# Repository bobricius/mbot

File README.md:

# mbot

2D actuator move micro robot in X/Y 2D space
Less than 10$ educational platform with micro magnetic robot (mBot), 
only 6 GPIO to move in unlimited X/Y 2D space

Great for physical education for languages like Karel and make 
SKOBAN game or solve acrylic cutted labyrinth. 

My project not violating SRI international patent 
(maybe, I am not patent expert) 

There is differences: 

- I am using another moving track configutation 
- Control is 3-phase unipolar against 4-phase bipolar 
- My manipulator (mBot) use 4 magnets and not levitating 
- For move in one dimension I need only 3x Mosfets connected to any MCU 
(Arduino Atmega328, Stm32, MSP430, ESP XXXX) 
- 6 GPIO to move in X/Y 2D space 
- Moving board can be produced in any fab, it is just only PCB board 8/8mil 
- IT IS CHEAP

PROJECT PAGE

https://hackaday.io/project/154496-2d-actuator-move-micro-robot-in-xy-2d-space

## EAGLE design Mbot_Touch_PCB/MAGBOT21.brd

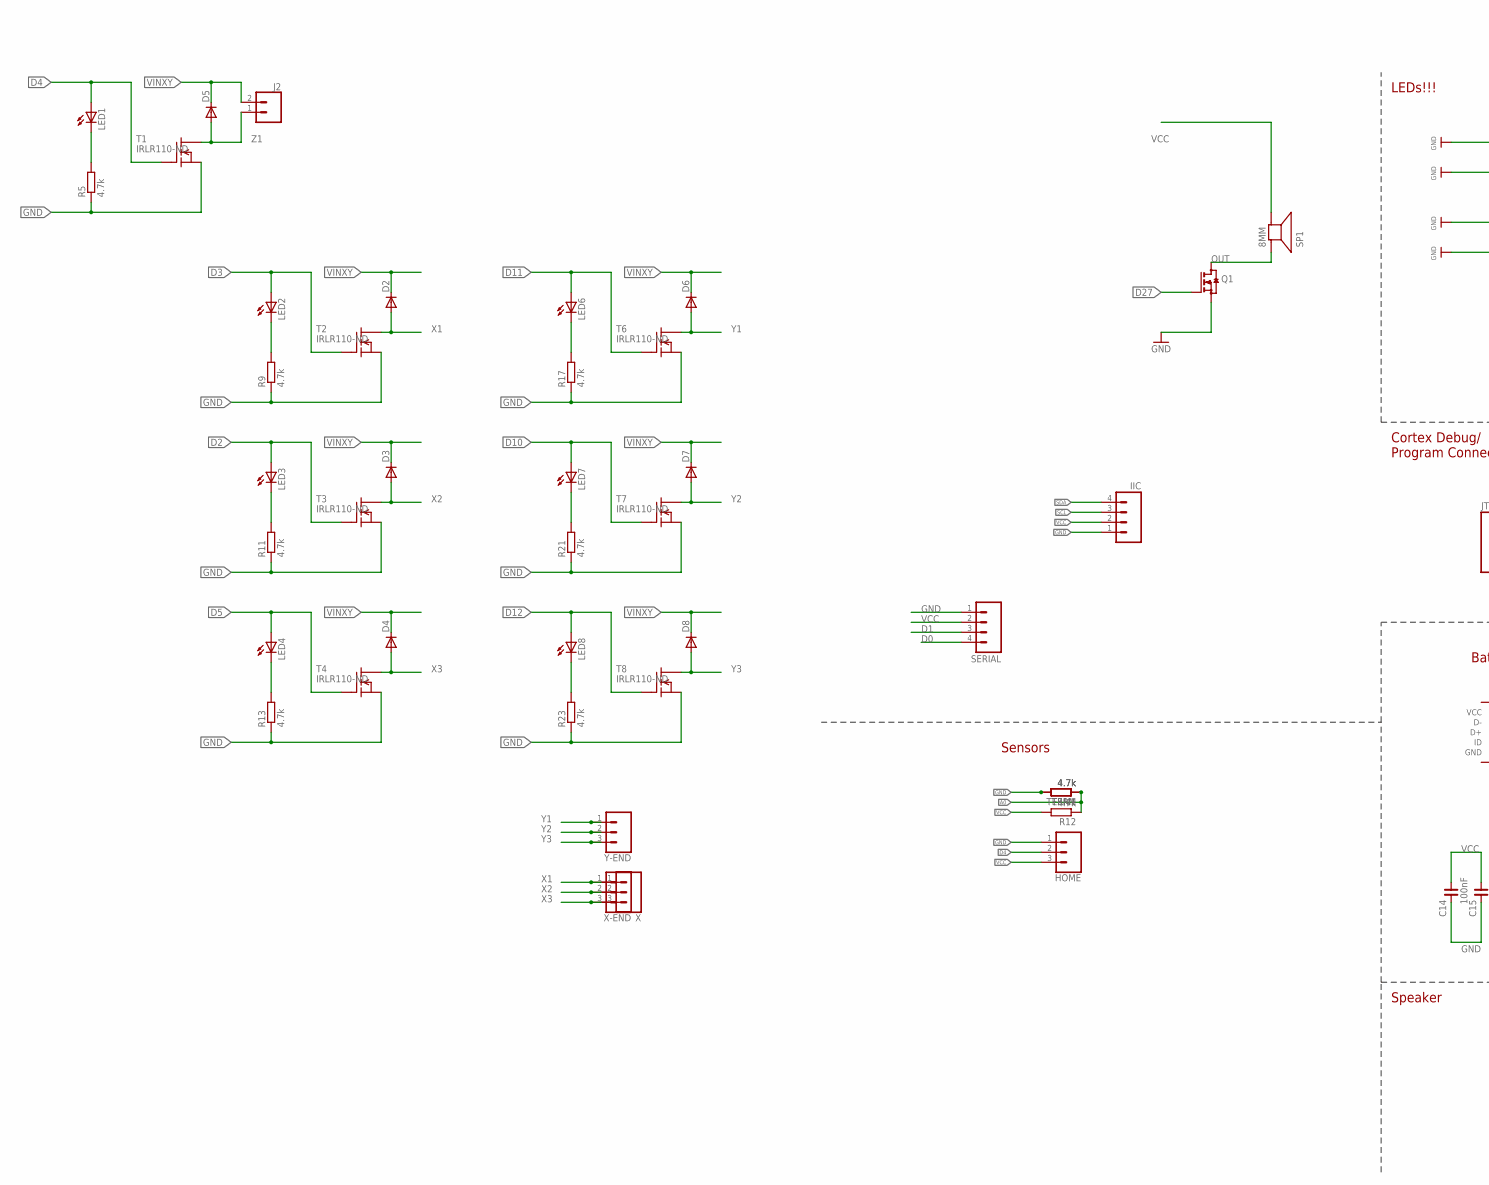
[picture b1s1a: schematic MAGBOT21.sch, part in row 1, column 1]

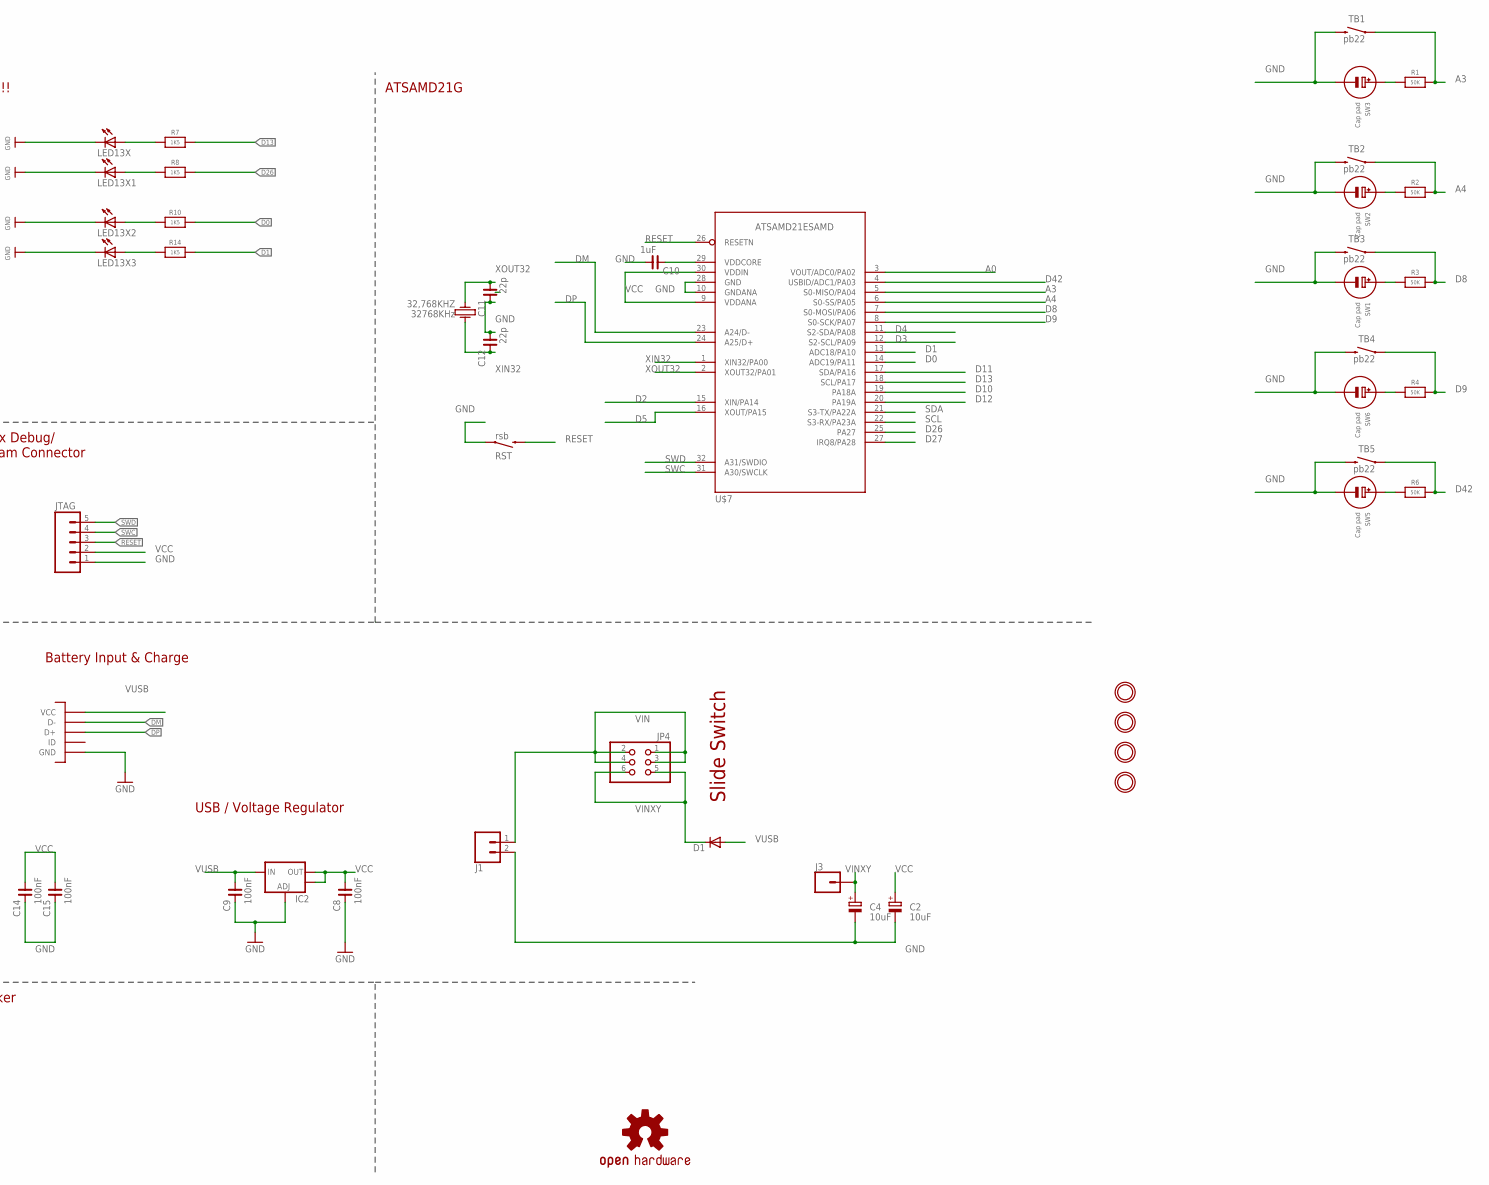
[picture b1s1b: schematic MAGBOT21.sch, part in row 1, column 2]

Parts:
32,768KHZ: 32768KHz; KX-327LT
C2, C4: 10uF; 153CLV-0605
C8, C9: 100nF; C0603
C10: 1uF; C0805
C11, C12: 22p; C0805
C14, C15: 100nF; C0805
D1, D2, D3, D4, D5, D6, D7, D8: DIODE-DO214AC; DO214AC
HOME: CONN_031X03_NO_SILK; 1X03_NO_SILK
IC2: V_REG_LM1117SOT223; SOT223
IIC: M041X04_NO_SILK; 1X04_NO_SILK
J1, J2: CONN_02PTH3; 1X02_LONGPADS
J3: CONN_01PTH_NO_SILK_KIT; 1X01NS_KIT
JP4: PINHD-2X3; 2X03
JTAG: M051.27MM; 1X05-1.27MM
LED1, LED2, LED3, LED4, LED6, LED7, LED8, LED13X, LED13X1: LEDCHIPLED_0805; CHIPLED_0805
LED13X2, LED13X3: LEDCHIPLED_0603; CHIPLED_0603
LOGO3: OSHW-LOGOS; OSHW-LOGO-S
Q1: BSS123; SOT23
R1, R2, R3, R4, R6: 50K; _0805
R5, R9, R11, R12, R13, R17, R21, R23: 4.7k; R0603
R7: 1K5; _0805MP
R8: 1K5; 0603-NO
R10, R14: 1K5; _0603MP
RST: rsb; TACTILE_SWITCH_SMD-3
SERIAL: M041X04_NO_SILK; 1X04_NO_SILK
SP1: 8MM; BUZZER_SMT_5MM
SW1, SW2, SW3, SW5, SW6: Cap pad; CAPTOUCH_SIMPLE_12.5MM
T1, T2, T3, T4, T6, T7, T8: IRLR110-ND; TO252
TB1, TB2, TB3, TB4, TB5: pb22; TACTILE_SWITCH_SMD-3
TERM, TERM1: 4.7k; R0805W
U$3, U$4, U$8, U$10: MOUNTINGHOLE2.0; MOUNTINGHOLE_2.0_PLATED
U$5: MICROUSB; MICRO_B
U$7: ATSAMD21ESAMD; TQFP32-08
X: CONN_031X03_NO_SILK; 1X03_NO_SILK
X-END: CONN_031X03_NO_SILK; 1X03_NO_SILK
Y-END: CONN_031X03_NO_SILK; 1X03_NO_SILK

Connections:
A0: R12.1, TERM.1, TERM1.1, U$7.3 (VOUT/ADC0/PA02)
A3: R1.1, TB1.1, U$7.5 (S0-MISO/PA04)
A4: R2.1, TB2.1, U$7.6 (S0-SS/PA05)
D0: R10.1, SERIAL.4, U$7.14 (ADC19/PA11)
D1: R14.1, SERIAL.3, U$7.13 (ADC18/PA10)
D2: LED3.A, T3.1 (G), U$7.15 (XIN/PA14)
D3: LED2.A, T2.1 (G), U$7.12 (S2-SCL/PA09)
D4: HOME.2, LED1.A, T1.1 (G), U$7.11 (S2-SDA/PA08)
D5: LED4.A, T4.1 (G), U$7.16 (XOUT/PA15)
D8: R3.1, TB3.1, U$7.7 (S0-MOSI/PA06)
D9: R4.1, TB4.1, U$7.8 (S0-SCK/PA07)
D10: LED7.A, T7.1 (G), U$7.19 (PA18A)
D11: LED6.A, T6.1 (G), U$7.17 (SDA/PA16)
D12: LED8.A, T8.1 (G), U$7.20 (PA19A)
D13: R7.1, U$7.18 (SCL/PA17)
D26: R8.1, U$7.25 (PA27)
D27: Q1.1 (G), U$7.27 (IRQ8/PA28)
D42: R6.1, TB5.1, U$7.4 (USBID/ADC1/PA03)
DM: U$5.P2 (D-), U$7.23 (A24/D-)
DP: U$5.P3 (D+), U$7.24 (A25/D+)
GND: C2.-, C4.-, C8.2, C9.2, C10.1, C11.2, C12.1, C14.2, C15.2, HOME.1, IC2.1 (ADJ), IIC.1, J1.2, JTAG.1, LED13X.C, LED13X1.C, LED13X2.C, LED13X3.C, Q1.2 (S), R5.1, R9.1, R11.1, R13.1, R17.1, R21.1, R23.1, RST.1, SERIAL.1, SW1.G (-), SW2.G (-), SW3.G (-), SW5.G (-), SW6.G (-), T1.2 (S), T2.2 (S), T3.2 (S), T4.2 (S), T6.2 (S), T7.2 (S), T8.2 (S), TB1.4 (2), TB2.4 (2), TB3.4 (2), TB4.4 (2), TB5.4 (2), TERM.2, TERM1.2, U$5.GND1 (GND), U$5.GND2 (GND), U$5.GND3 (GND), U$5.GND4 (GND), U$5.GND7 (GND), U$5.GND8 (GND), U$5.P5 (GND), U$7.10 (GNDANA), U$7.28 (GND)
unnamed: R6.2, SW5.E (+)
unnamed: R4.2, SW6.E (+)
unnamed: R3.2, SW1.E (+)
unnamed: R2.2, SW2.E (+)
unnamed: R1.2, SW3.E (+)
unnamed: LED13X1.A, R8.2
unnamed: LED2.C, R9.2
unnamed: LED6.C, R17.2
unnamed: C10.2, U$7.29 (VDDCORE)
unnamed: LED3.C, R11.2
unnamed: LED7.C, R21.2
unnamed: LED4.C, R13.2
unnamed: LED8.C, R23.2
unnamed: LED13X.A, R7.2
unnamed: LED1.C, R5.2
unnamed: LED13X2.A, R10.2
unnamed: LED13X3.A, R14.2
OUT: Q1.3 (D), SP1.+
RESET: JTAG.3, RST.4 (2), U$7.26 (RESETN)
SCL: IIC.3, U$7.22 (S3-RX/PA23A)
SDA: IIC.4, U$7.21 (S3-TX/PA22A)
SWC: JTAG.4, U$7.31 (A30/SWCLK)
SWD: JTAG.5, U$7.32 (A31/SWDIO)
VCC: C2.+, C8.1, C14.1, C15.1, HOME.3, IC2.2 (OUT), IC2.4 (OUT), IIC.2, JTAG.2, R12.2, SERIAL.2, SP1.-, U$7.9 (VDDANA), U$7.30 (VDDIN)
VIN: J1.1, JP4.1, JP4.2, JP4.3, JP4.4
VINXY: C4.+, D1.C, D2.C, D3.C, D4.C, D5.C, D6.C, D7.C, D8.C, J2.2, J3.1, JP4.5, JP4.6
VUSB: C9.1, D1.A, IC2.3 (IN), U$5.P1 (VCC)
X1: D2.A, T2.3 (D), X.1, X-END.1
X2: D3.A, T3.3 (D), X.2, X-END.2
X3: D4.A, T4.3 (D), X.3, X-END.3
XIN32: 32,768KHZ.1, C12.2, U$7.1 (XIN32/PA00)
XOUT32: 32,768KHZ.4, C11.1, U$7.2 (XOUT32/PA01)
Y1: D6.A, T6.3 (D), Y-END.1
Y2: D7.A, T7.3 (D), Y-END.2
Y3: D8.A, T8.3 (D), Y-END.3
Z1: D5.A, J2.1, T1.3 (D)

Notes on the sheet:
USB / Voltage Regulator
LEDs!!!
Cortex Debug/ Program Connector
Sensors
ATSAMD21G
Battery Input & Charge
Speaker
Slide Switch

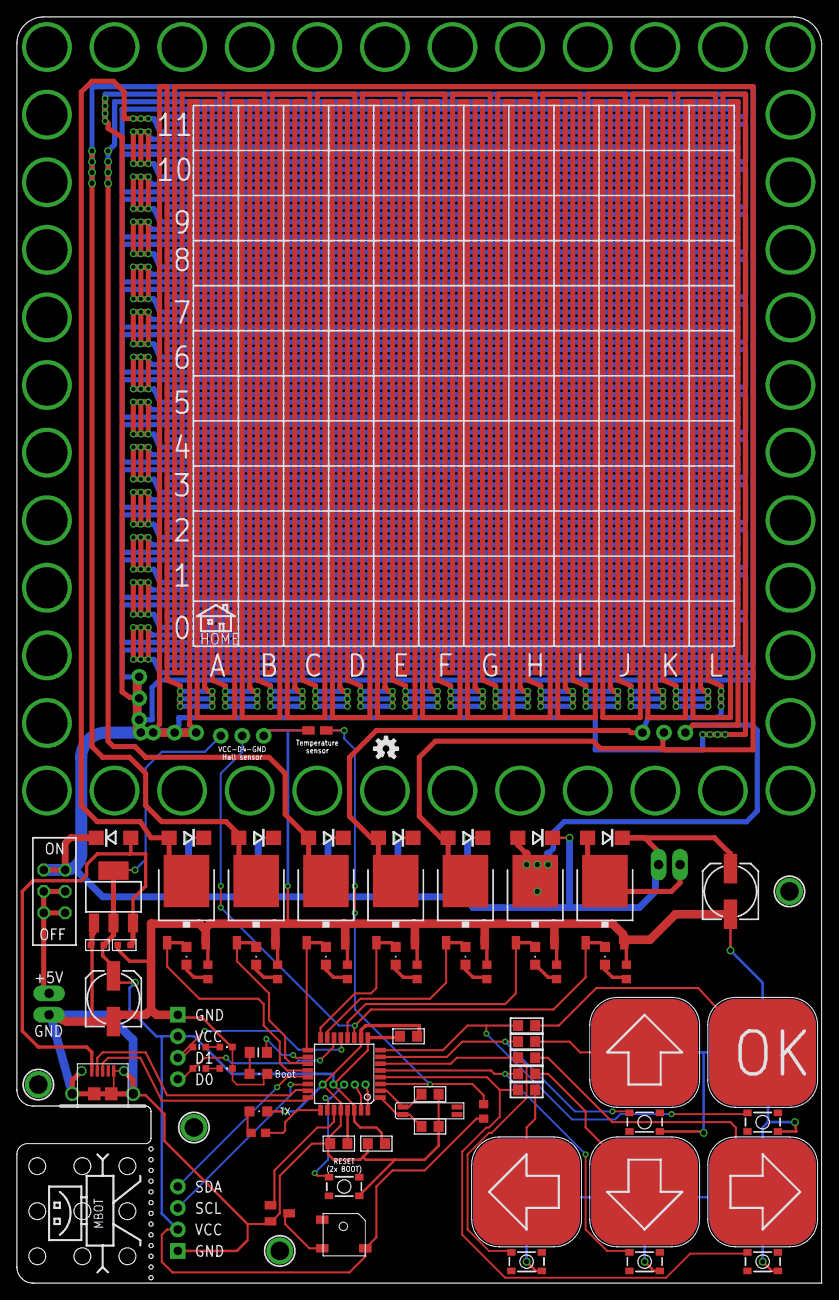
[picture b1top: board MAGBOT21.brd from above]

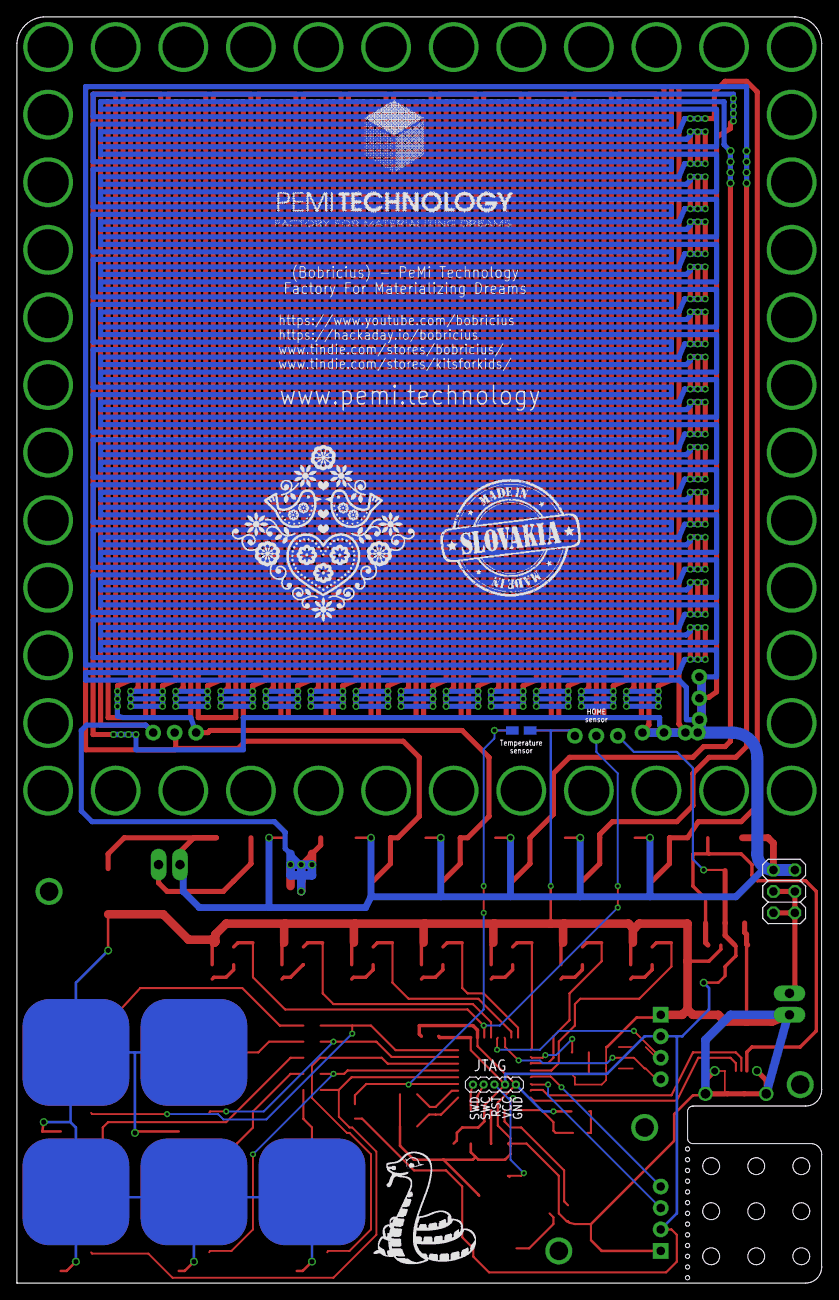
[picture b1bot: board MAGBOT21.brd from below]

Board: 2 copper layers, 95.2 x 149.9 mm, 87 parts (4 on the bottom side), 57 nets.

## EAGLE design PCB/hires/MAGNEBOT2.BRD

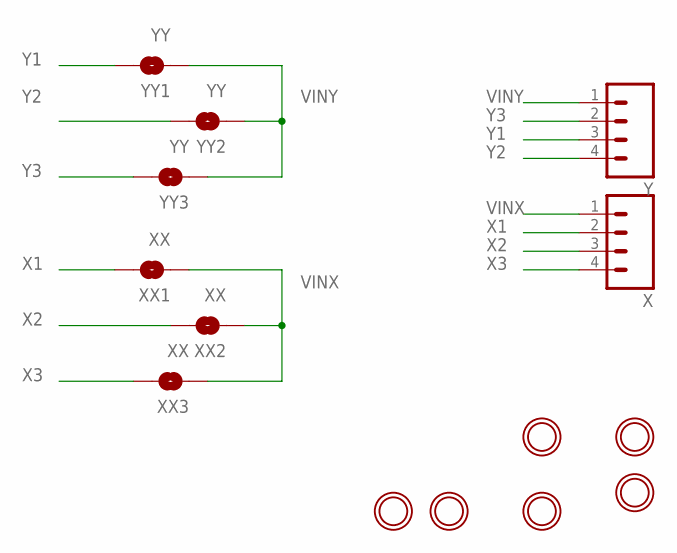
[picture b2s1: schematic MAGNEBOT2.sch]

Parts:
U$1, U$2, U$3, U$4, U$5, U$10: MOUNTINGHOLE2.0; MOUNTINGHOLE_2.0_PLATED
X: M04PTH; 1X04
XX1, XX2, XX3: XX; SJ_2S-TRACE
Y: M04PTH; 1X04
YY1, YY2, YY3: YY; SJ_2S-TRACE

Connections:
VINX: X.1, XX1.1, XX2.1, XX3.1
VINY: Y.1, YY1.1, YY2.1, YY3.1
X1: X.2, XX1.2
X2: X.3, XX2.2
X3: X.4, XX3.2
Y1: Y.3, YY1.2
Y2: Y.4, YY2.2
Y3: Y.2, YY3.2

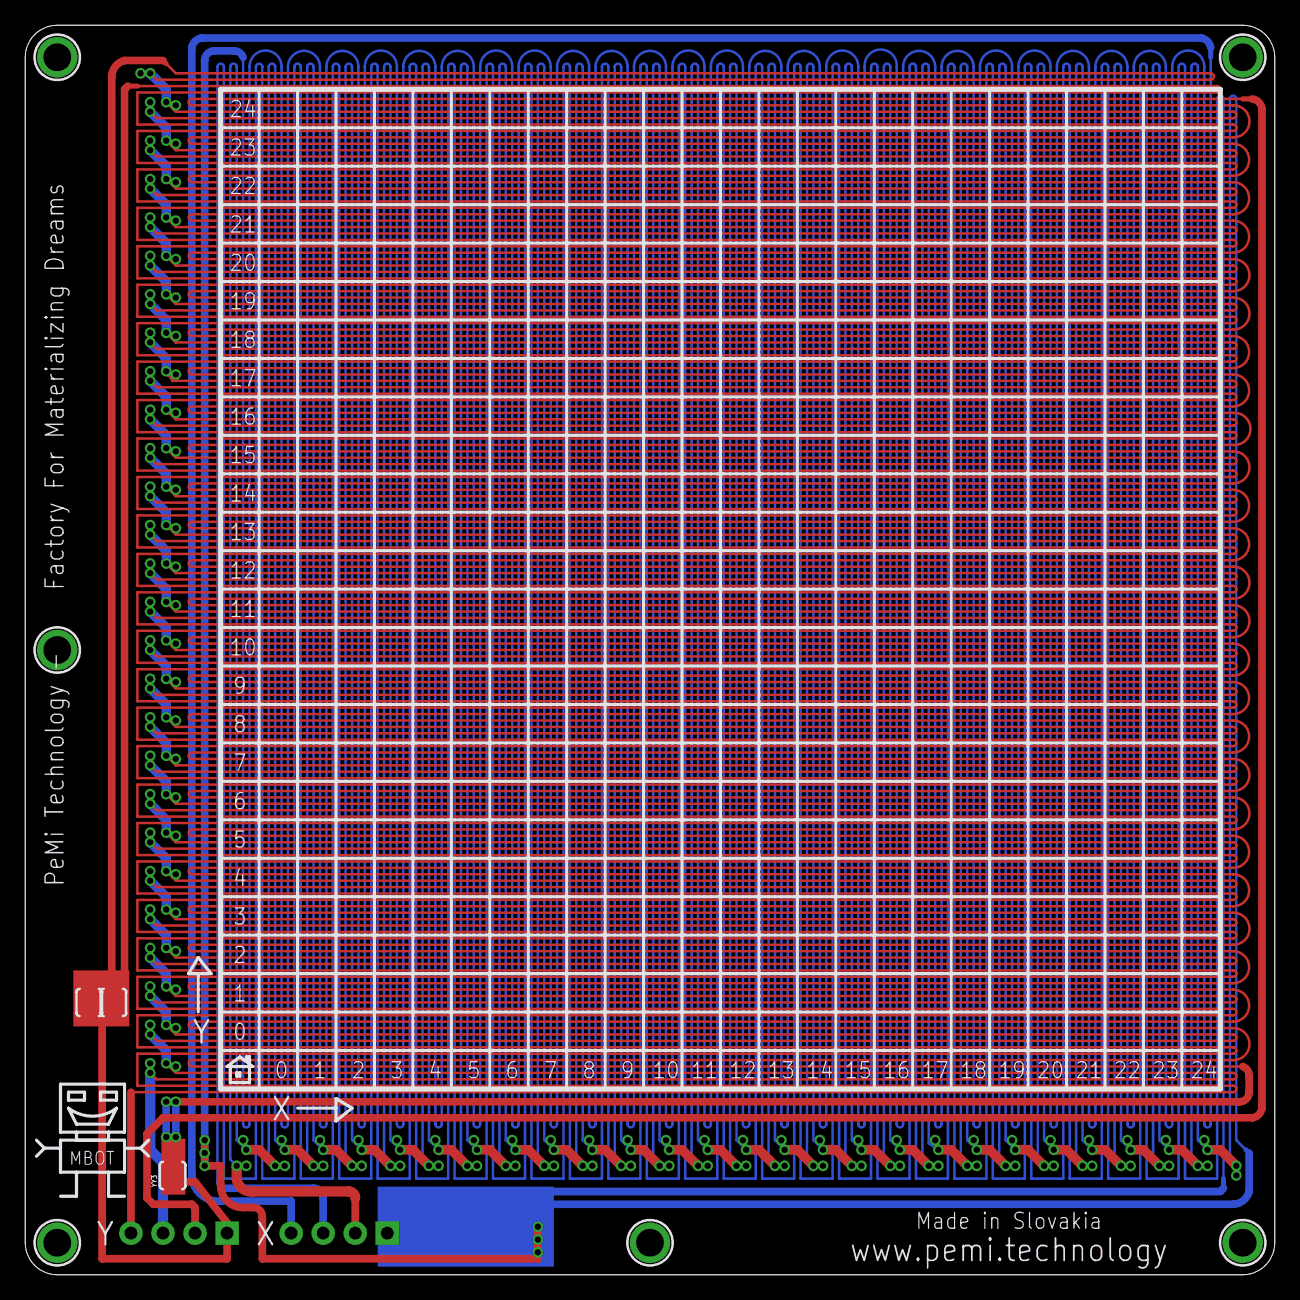
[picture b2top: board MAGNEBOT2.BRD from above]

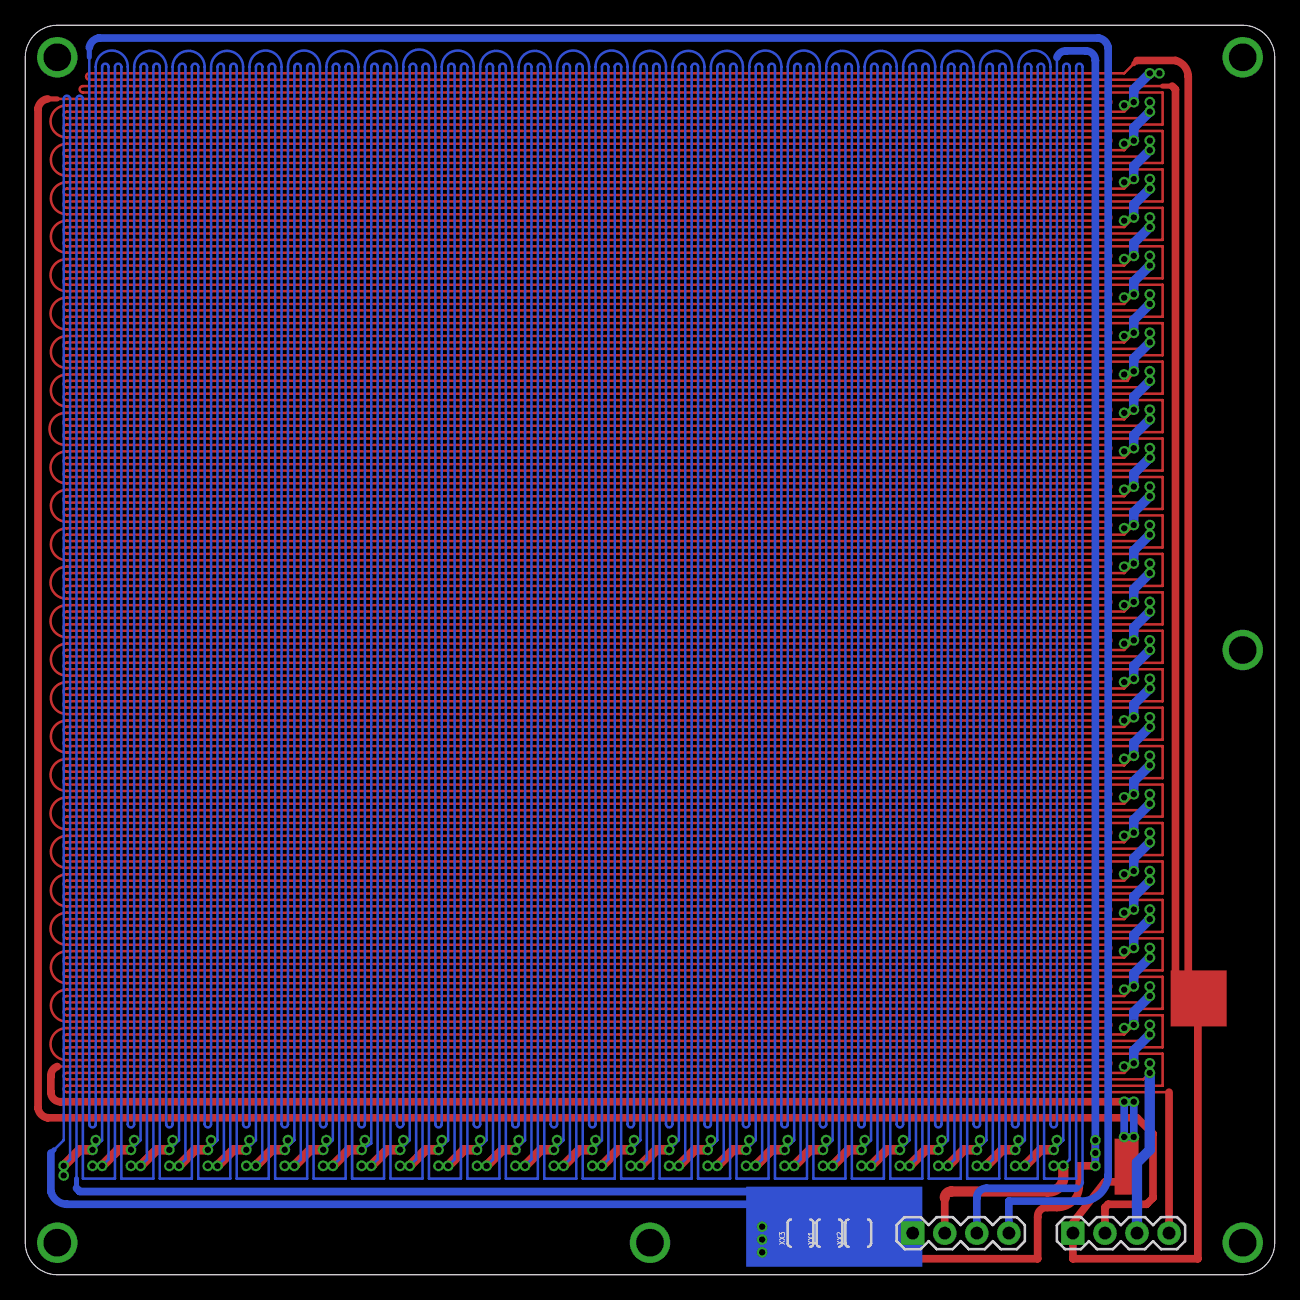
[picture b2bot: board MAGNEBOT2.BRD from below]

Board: 2 copper layers, 99.1 x 99.1 mm, 14 parts (5 on the bottom side), 8 nets.

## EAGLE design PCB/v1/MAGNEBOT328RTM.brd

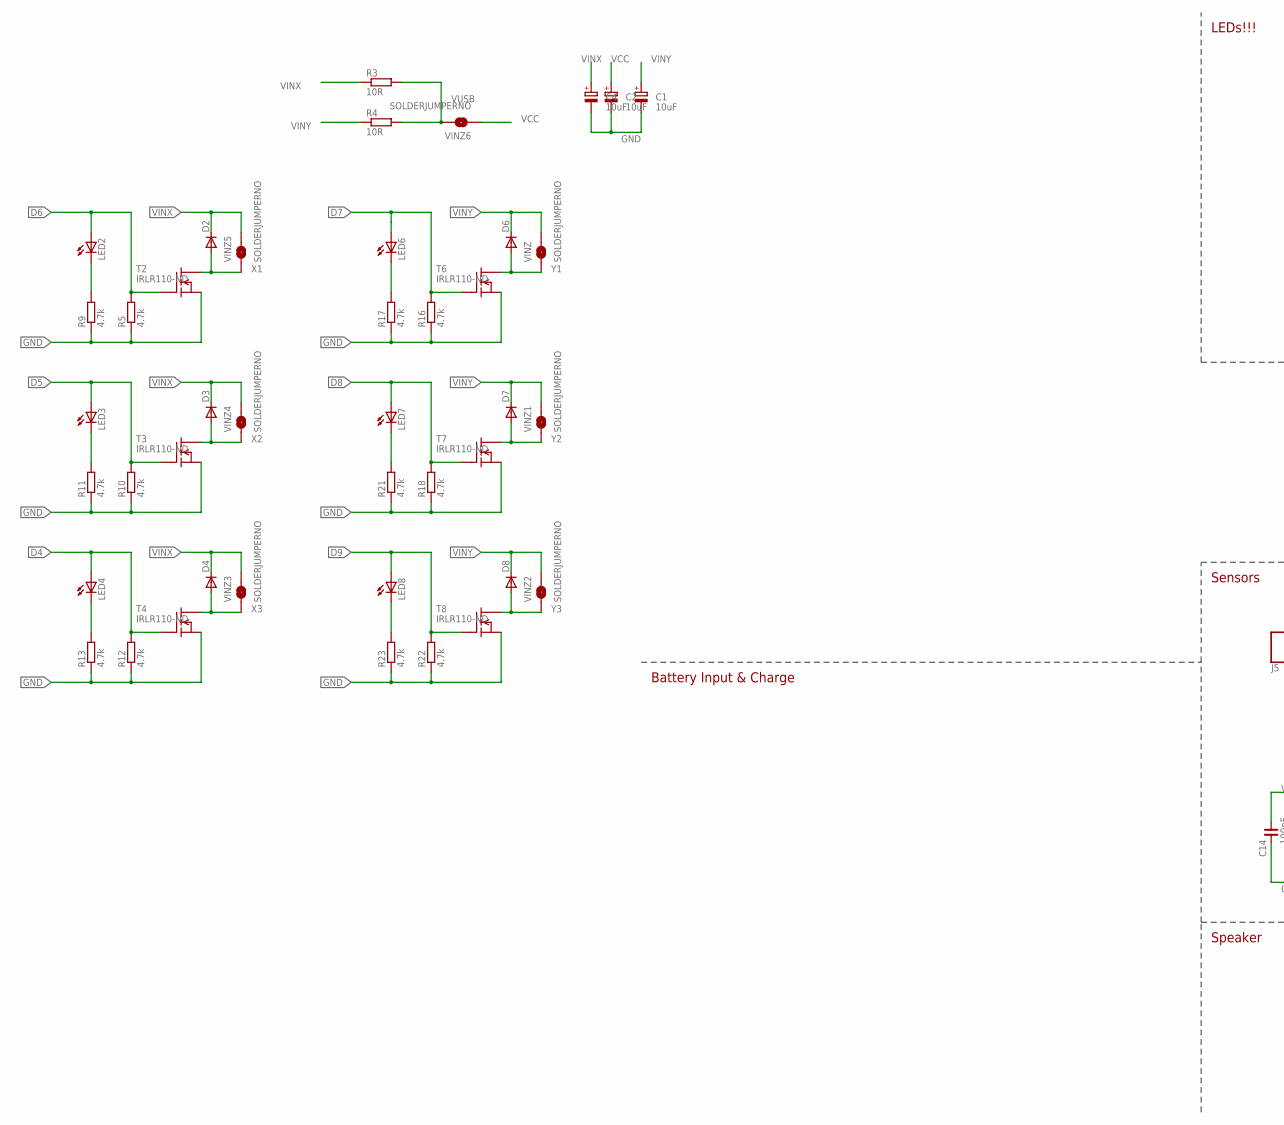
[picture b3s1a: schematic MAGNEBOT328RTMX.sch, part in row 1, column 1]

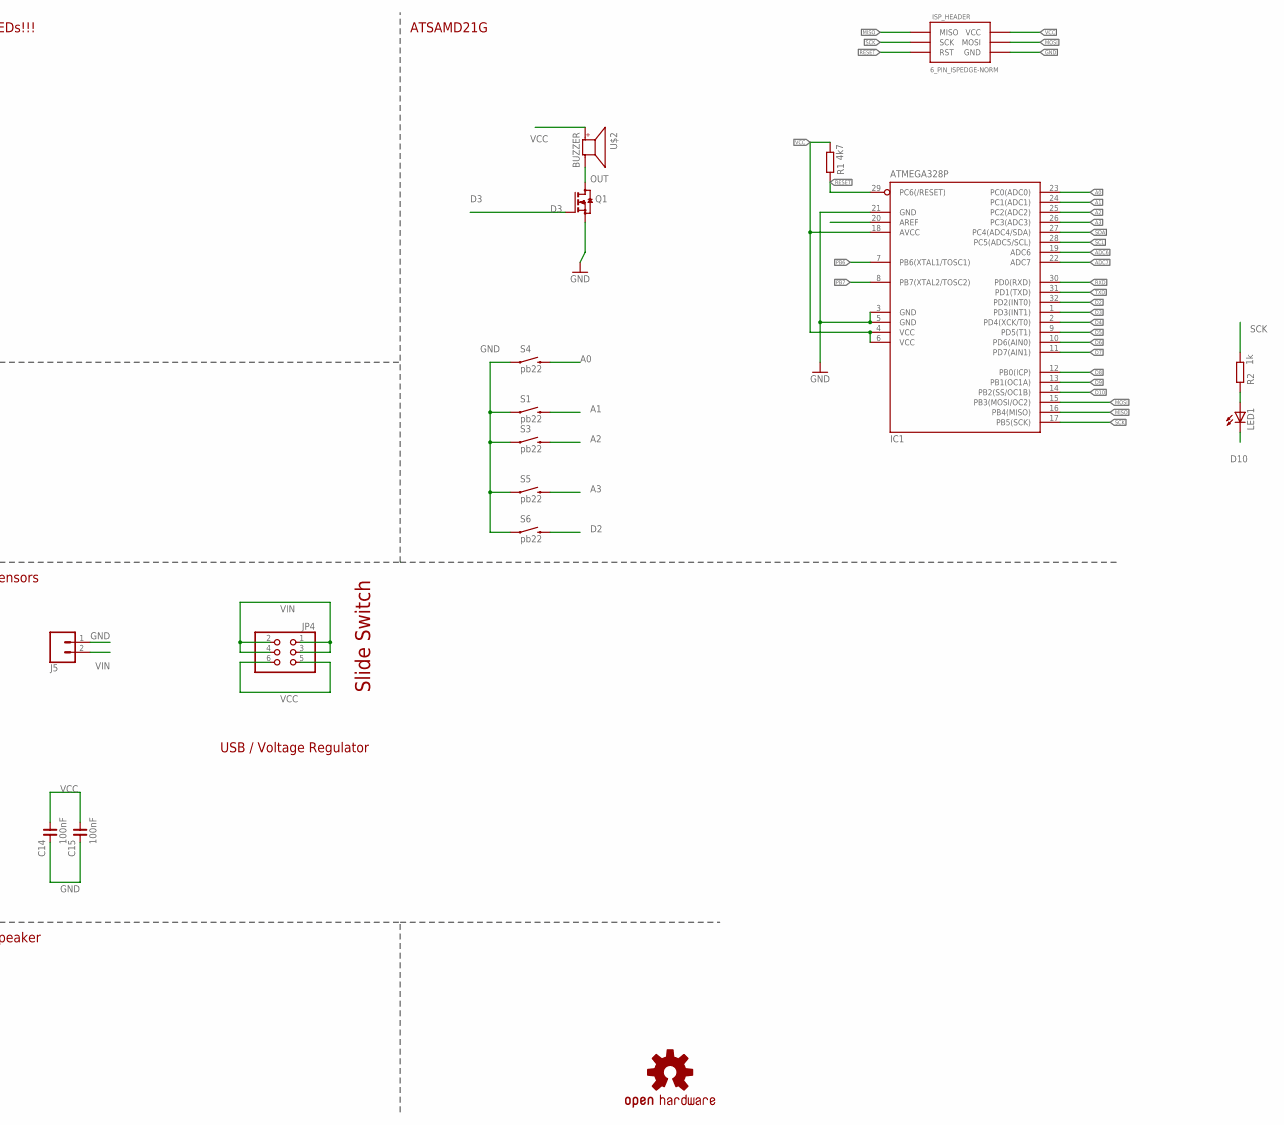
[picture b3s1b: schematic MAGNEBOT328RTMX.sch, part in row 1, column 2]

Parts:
C1, C2, C4: 10uF; E2,5-7
C14, C15: 100nF; C0603
D2, D3, D4, D6, D7, D8: DIODE-DO214AC; DO214AC
IC1: ATMEGA328P; TQFP32-08
ISP_HEADER: 6_PIN_ISPEDGE-NORM; 6_PIN_EDGE
J5: CONN_02PTH3; 1X02_LONGPADS
JP4: PINHD-2X3; 2X03
LED1: LEDCHIPLED_0603; CHIPLED_0603
LED2: LEDCHIP-LED0805; CHIP-LED0805
LED3, LED4, LED6, LED7, LED8: LEDCHIPLED_0805; CHIPLED_0805
LOGO3: OSHW-LOGOS; OSHW-LOGO-S
Q1: BSS123; SOT23
R1: 4k7; R0603
R2: 1k; R0603
R3, R4: 10R; 0309/12
R5, R9, R10, R11, R12, R13, R16, R17, R18, R21, R22, R23: 4.7k; R0603
S1, S3, S4, S5, S6: pb22; TACTILE-PTH
T2, T3, T4, T6, T7, T8: IRLR110-ND; TO252
U$2: BUZZER; SMT-8585-BUZZER
VINZ, VINZ1, VINZ2, VINZ3, VINZ4, VINZ5, VINZ6: SOLDERJUMPERNO; SJ_2S-NO

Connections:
A0: IC1.23 (PC0(ADC0)), S4.3 (2)
A1: IC1.24 (PC1(ADC1)), S1.3 (2)
A2: IC1.25 (PC2(ADC2)), S3.3 (2)
A3: IC1.26 (PC3(ADC3)), S5.3 (2)
ADC6: IC1.19 (ADC6)
ADC7: IC1.22 (ADC7)
AREF: IC1.20 (AREF)
D2: IC1.32 (PD2(INT0)), S6.3 (2)
D3: IC1.1 (PD3(INT1)), Q1.1 (G)
D4: IC1.2 (PD4(XCK/T0)), LED4.A, R12.2, T4.1 (G)
D5: IC1.9 (PD5(T1)), LED3.A, R10.2, T3.1 (G)
D6: IC1.10 (PD6(AIN0)), LED2.A, R5.2, T2.1 (G)
D7: IC1.11 (PD7(AIN1)), LED6.A, R16.2, T6.1 (G)
D8: IC1.12 (PB0(ICP)), LED7.A, R18.2, T7.1 (G)
D9: IC1.13 (PB1(OC1A)), LED8.A, R22.2, T8.1 (G)
D10: IC1.14 (PB2(SS/OC1B)), LED1.C
GND: C1.-, C2.-, C4.-, C14.2, C15.2, IC1.3 (GND), IC1.5 (GND), IC1.21 (GND), ISP_HEADER.6 (GND), J5.1, Q1.2 (S), R5.1, R9.1, R10.1, R11.1, R12.1, R13.1, R16.1, R17.1, R18.1, R21.1, R22.1, R23.1, S1.1, S3.1, S4.1, S5.1, S6.1, T2.2 (S), T3.2 (S), T4.2 (S), T6.2 (S), T7.2 (S), T8.2 (S)
MISO: IC1.16 (PB4(MISO)), ISP_HEADER.1 (MISO)
MOSI: IC1.15 (PB3(MOSI/OC2)), ISP_HEADER.4 (MOSI)
unnamed: LED1.A, R2.2
unnamed: LED2.C, R9.2
unnamed: LED6.C, R17.2
unnamed: LED3.C, R11.2
unnamed: LED7.C, R21.2
unnamed: LED4.C, R13.2
unnamed: LED8.C, R23.2
OUT: Q1.3 (D), U$2.-
PB6: IC1.7 (PB6(XTAL1/TOSC1))
PB7: IC1.8 (PB7(XTAL2/TOSC2))
RESET: IC1.29 (PC6(/RESET)), ISP_HEADER.5 (RST), R1.2
RXD: IC1.30 (PD0(RXD))
SCK: IC1.17 (PB5(SCK)), ISP_HEADER.3 (SCK), R2.1
SCL: IC1.28 (PC5(ADC5/SCL))
SDA: IC1.27 (PC4(ADC4/SDA))
TXD: IC1.31 (PD1(TXD))
VCC: C2.+, C14.1, C15.1, IC1.4 (VCC), IC1.6 (VCC), IC1.18 (AVCC), ISP_HEADER.2 (VCC), JP4.5, JP4.6, R1.1, U$2.+, VINZ6.1
VIN: J5.2, JP4.1, JP4.2, JP4.3, JP4.4
VINX: C4.+, D2.C, D3.C, D4.C, R3.1, VINZ3.2, VINZ4.2, VINZ5.2
VINY: C1.+, D6.C, D7.C, D8.C, R4.1, VINZ.2, VINZ1.2, VINZ2.2
VUSB: R3.2, R4.2, VINZ6.2
X1: D2.A, T2.3 (D), VINZ5.1
X2: D3.A, T3.3 (D), VINZ4.1
X3: D4.A, T4.3 (D), VINZ3.1
Y1: D6.A, T6.3 (D), VINZ.1
Y2: D7.A, T7.3 (D), VINZ1.1
Y3: D8.A, T8.3 (D), VINZ2.1

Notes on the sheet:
USB / Voltage Regulator
LEDs!!!
Sensors
ATSAMD21G
Battery Input & Charge
Speaker
Slide Switch

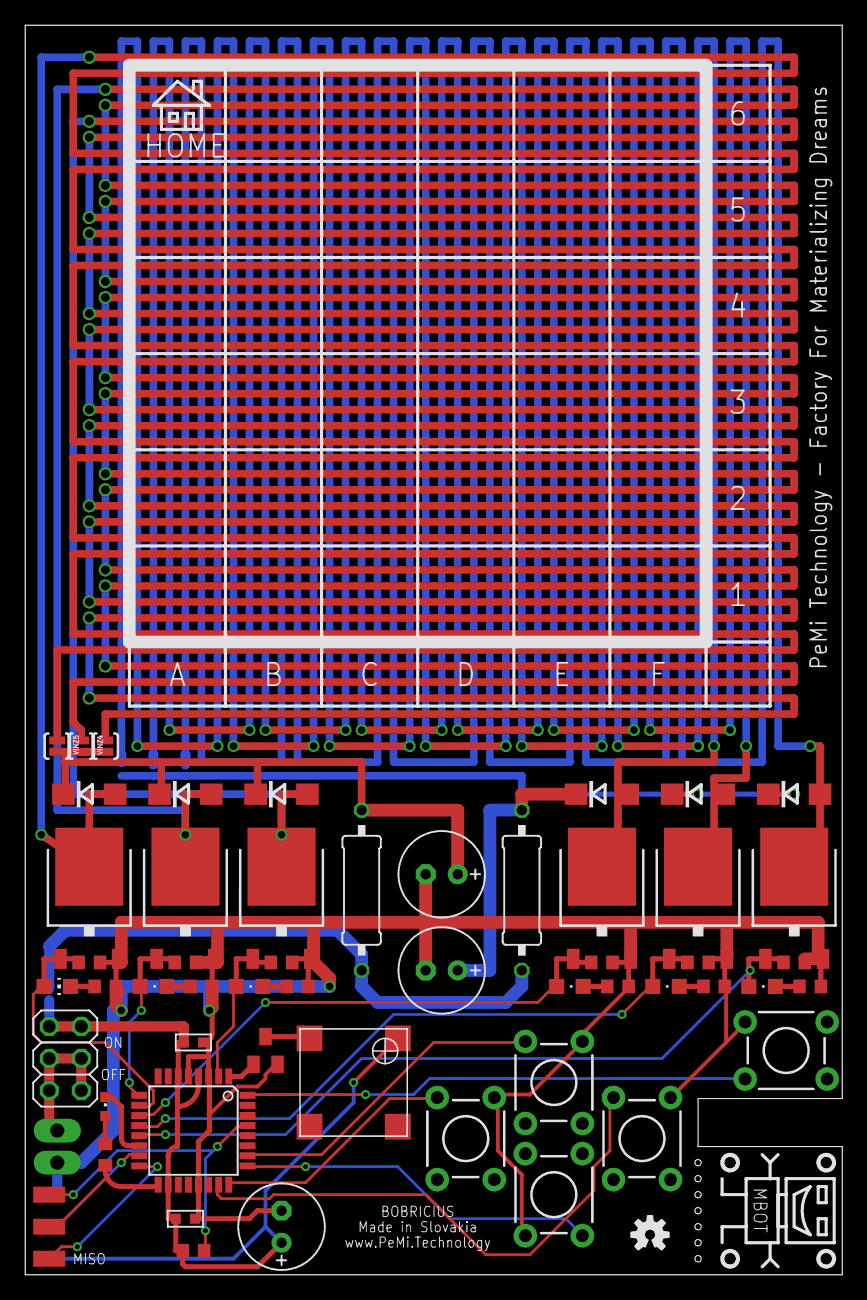
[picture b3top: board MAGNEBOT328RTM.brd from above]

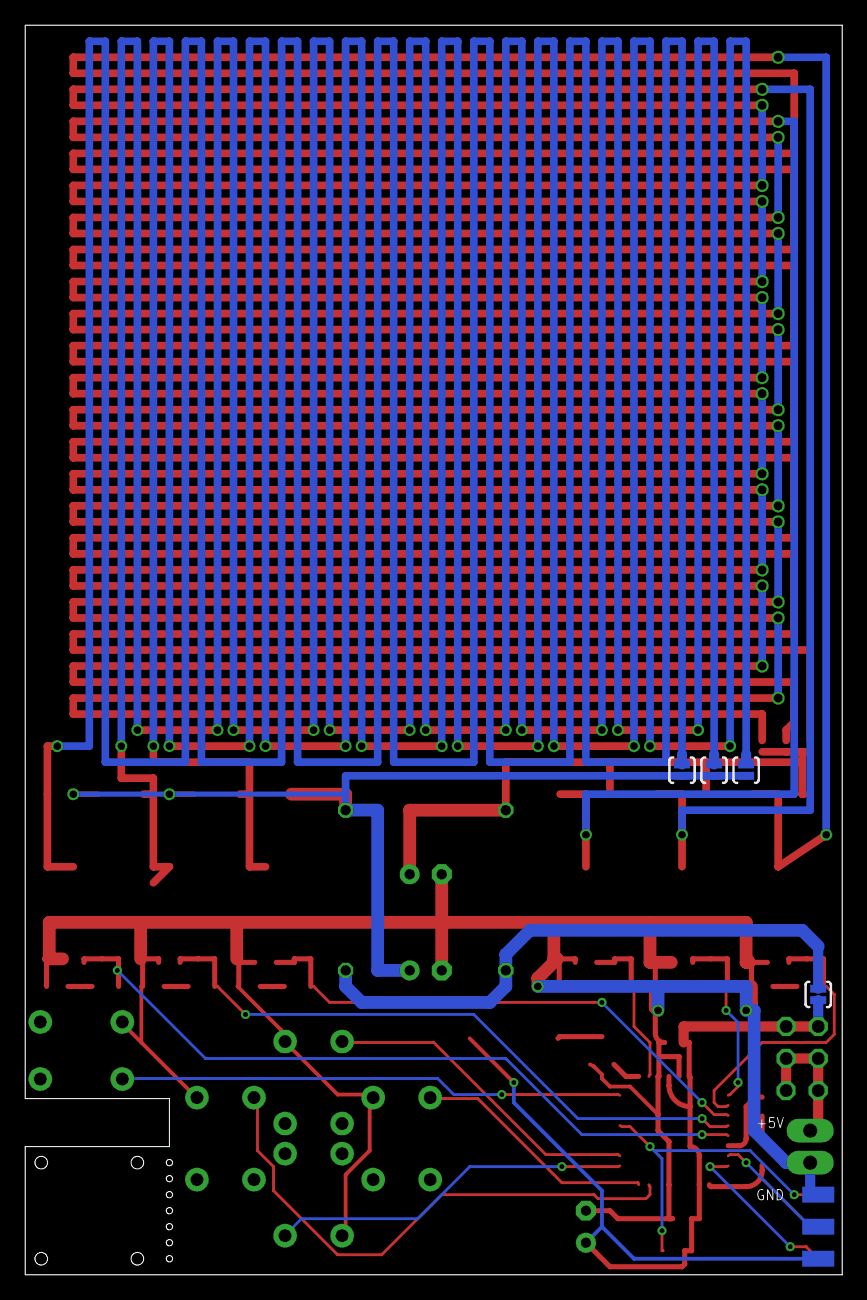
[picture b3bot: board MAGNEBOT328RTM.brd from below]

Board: 2 copper layers, 64.8 x 99.1 mm, 59 parts (4 on the bottom side), 37 nets.

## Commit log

2019-05-19 Touch version

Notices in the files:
parts and their libraries:
SparkFun-Aesthetics: Licensing: Creative Commons ShareAlike 4.0 International - https://creativecommons.org/licenses/by-sa/4.0
